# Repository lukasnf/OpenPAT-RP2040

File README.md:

# OpenPAT-RP2040

> **⚠️ SAFETY DISCLAIMER:** This project is for educational and preliminary diagnostic purposes only. While it tests electrical safety parameters, it is **not** a certified Portable Appliance Tester (PAT). It does not replace legally required safety tests conducted with calibrated and certified equipment. Always assume appliances are dangerous until proven otherwise.

**OpenPAT-RP2040** is a low-voltage Portable Appliance Tester based on the RP2040 microcontroller. It is designed to safely measure Protective Earth (PE) continuity at standard test currents (200mA) and verify Phase-to-Neutral (L-N) resistance on **unpowered** appliances. 

Operating completely without high measurement voltages, this design allows for safe preliminary testing of appliances. 

> **Note:** This project is currently under active development. The schematics and PCB layout have been designed using KiCad and manufactured via JLCPCB.

---

## 🛠 Hardware Architecture

The measurement circuitry is designed around the RP2040 and relies on a dedicated analog frontend for precise, low-voltage readings. Based on the schematic, the core components and sub-circuits include:

* **Microcontroller:** RP2040
* **Analog-to-Digital Converter (ADC):** ADS1115 connected via I2C (`I2C_SCL`, `I2C_SDA`) to read the measurement nodes (`PE_TEST`, `PE_TEST_RE`, `L_T`, `N_T`).
* **PE Test Current Source:** A constant current source generating approximately 200mA. This is achieved using an LM317 linear regulator (U1) combined with a 6.2Ω / 1W resistor (R1).
* **PE Continuity Measurement:** Employs a **4-wire (Kelvin) measurement method** to accurately determine resistance by eliminating the voltage drop across the test leads. This is implemented using separate connections for force (`PE_FORCE_IN`, `PE_OUT1`) and sense (`PE_SENSE_1`, which connects to the protected `PE_TEST_RE` node).
* **L-N Resistance Measurement:** Controlled via RP2040 GPIOs. An NMOS transistor (Q1, controlled by GP26) and a switched pull-up (via GP27 and a 1kΩ resistor) are used to configure the circuit to measure the resistance between the Phase and Neutral test points via the L/N_TEST1 connector.
* **Input Protection:** All sensitive analog measurement lines are protected against transients. The circuit uses 10kΩ series resistors (R2, R3, R4, R5) and BAT54S dual Schottky diodes (D1, D2, D3, D4) to safely clamp the ADC inputs to the 3.3V rail and Ground.

## Components

| Component | Value / Type |
| :--- | :--- | 
| Microcontroller | RP2040 Zero 
| ADC | ADS1115 
| N-Channel MOSFET | IRLML 2502 (20V, 4.2A, SOT-23) 
| Schottky Diode | BAT54S-7-F (30V, 0.2A, SOT23) 
| Capacitor | 100 nF (50V, X7R, RM 2.5) 
| Terminal Block | MKDS 1.5/2-5.08 (2-pin, RM 5.08) 
| Shunt Resistor | 6.2 Ω (1 Watt) 
| Standard Resistors | 10 kΩ, 1 kΩ 

## 📂 Repository Contents

...

## 📄 License

This repository contains both hardware design files and software source code, which are licensed differently:

* **Hardware:** All hardware design files (schematics, PCB layouts) are released under the [CERN Open Hardware Licence Version 2 - Strongly Reciprocal (CERN-OHL-S v2)](LICENSE).
* **Software:** All source code is released under the [MIT License](LICENSE-MIT).

This README was drafted with AI assistance. All technical information has been manually verified by the author.

Lukas F.

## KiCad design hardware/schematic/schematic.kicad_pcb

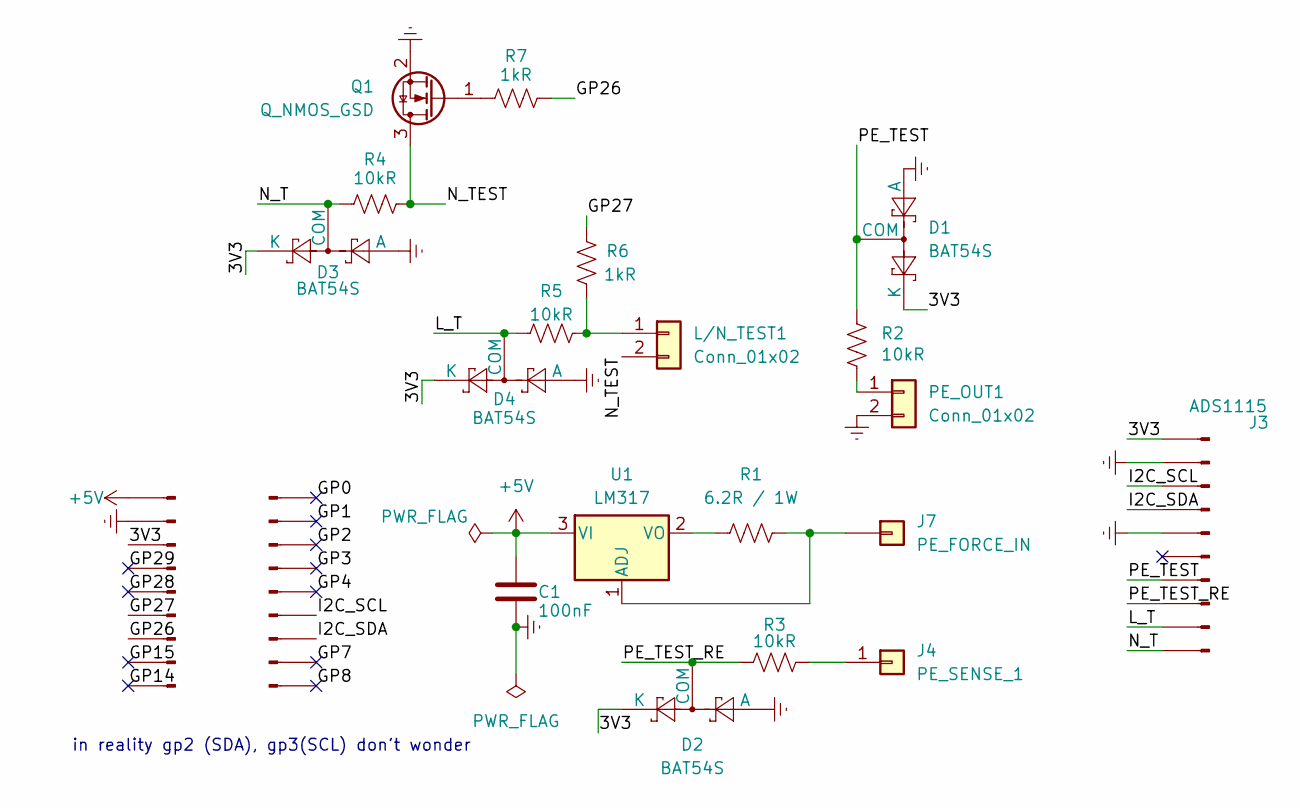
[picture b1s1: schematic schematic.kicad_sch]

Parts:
C1: 100nF; C_Disc_D5.0mm_W2.5mm_P2.50mm
D1, D2, D3, D4: BAT54S; SOT-23; LCSC C83574
J1, J2: Conn_01x09_Pin; PinHeader_1x09_P2.54mm_Vertical
J3: ADS1115; PinHeader_1x10_P2.54mm_Vertical
J4: PE_SENSE_1; PinHeader_1x01_P2.54mm_Vertical
J7: PE_FORCE_IN; PinHeader_1x01_P2.54mm_Vertical
L/N_TEST1: Conn_01x02; TerminalBlock_Phoenix_MKDS-1,5-2-5.08_1x02_P5.08mm_Horizont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
PE_OUT1: Conn_01x02; TerminalBlock_Phoenix_MKDS-1,5-2-5.08_1x02_P5.08mm_Horizont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
Q1: Q_NMOS_GSD; SOT-23; LCSC C20917
R1: 6.2R / 1W; R_Axial_DIN0411_L9.9mm_D3.6mm_P12.70mm_Horizontal
R2, R3, R4, R5: 10kR; R_Axial_DIN0207_L6.3mm_D2.5mm_P10.16mm_Horizontal
R6, R7: 1kR; R_Axial_DIN0207_L6.3mm_D2.5mm_P10.16mm_Horizontal
U1: LM317; TO-220-3_Vertical

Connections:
+5V: C1.1, J2.9, U1.3 (VI)
/3V3: D1.2 (K), D2.2 (K), D3.2 (K), D4.2 (K), J2.7, J3.10
/GP0: J1.1
/GP1: J1.2
/GP2: J1.3
/GP3: J1.4
/GP4: J1.5
/GP7: J1.8
/GP8: J1.9
/GP14: J2.1
/GP15: J2.2
/GP26: J2.3, R7.2
/GP27: J2.4, R6.1
/GP28: J2.5
/GP29: J2.6
/I2C_SCL: J1.6, J3.8
/I2C_SDA: J1.7, J3.7
/L_T: D4.3 (COM), J3.2, R5.1
/N_T: D3.3 (COM), J3.1, R4.1
/N_TEST: L/N_TEST1.2, Q1.3 (D), R4.2
/PE_TEST: D1.3 (COM), J3.4, R2.1
/PE_TEST_RE: D2.3 (COM), J3.3, R3.2
GNDREF: C1.2, D1.1 (A), D2.1 (A), D3.1 (A), D4.1 (A), J2.8, J3.6, J3.9, PE_OUT1.2, Q1.2 (S)
unnamed: J4.1 (Pin_1_1), R3.1
unnamed: J7.1 (Pin_1_1), R1.2, U1.1 (ADJ)
unnamed: L/N_TEST1.1, R5.2, R6.2
unnamed: PE_OUT1.1, R2.2
unnamed: Q1.1 (G), R7.1
unnamed: R1.1, U1.2 (VO)

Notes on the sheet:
in reality gp2 (SDA), gp3(SCL) don't wonder

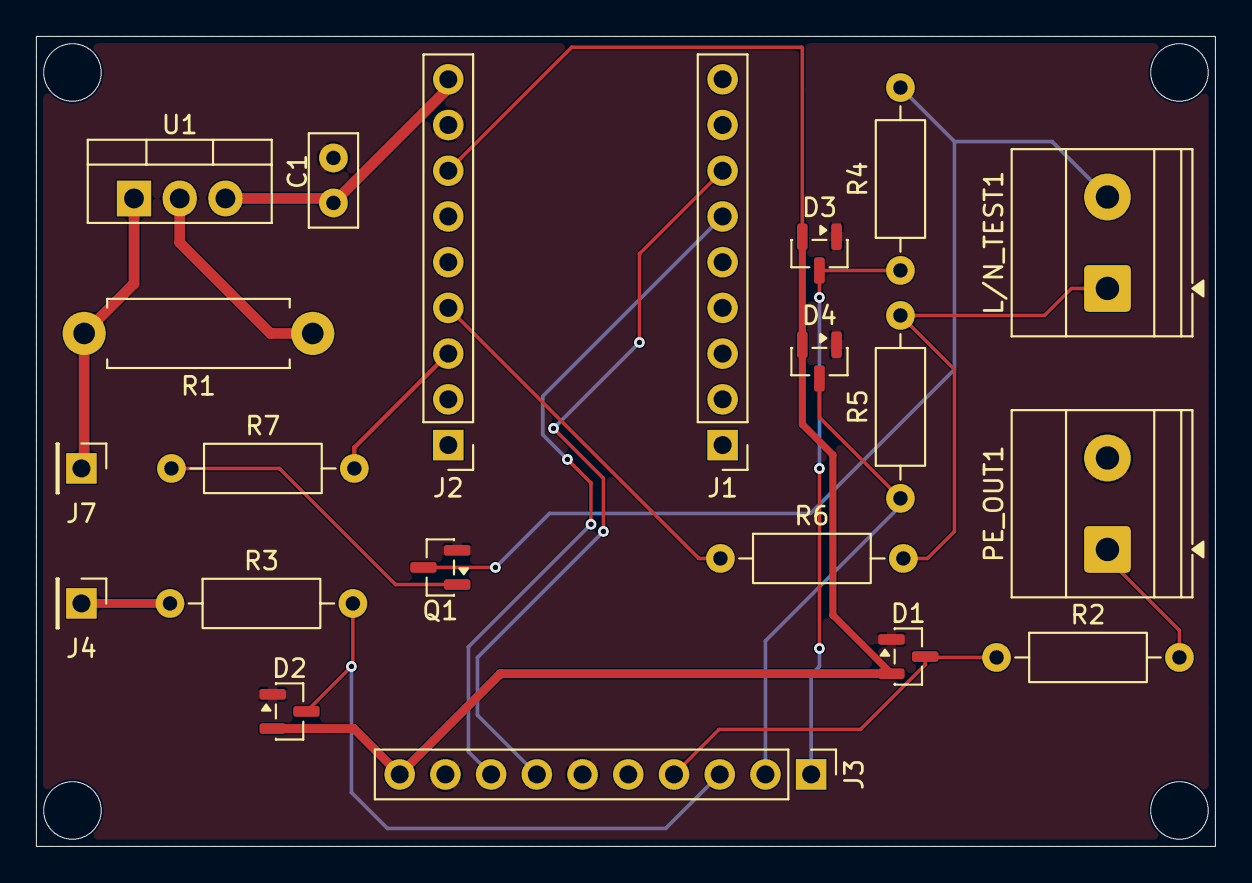
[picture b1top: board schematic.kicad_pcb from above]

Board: 2 copper layers, 65.5 x 45.0 mm, 21 parts (0 on the bottom side), 18 nets.

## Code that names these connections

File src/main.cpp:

#include <Arduino.h>
#include <Wire.h>
#include <Adafruit_ADS1X15.h>

Adafruit_ADS1115 ads; 

// pin definitions
const int MOSFET_GATE = 26; // GPIO 26 for MOSFET gate
const int L_DRIVE = 27; // GPIO 27 for L drive

// ADS pins definitions
const int ADS_PE_HIGH = 0; // PE_TEST_RE
const int ADS_PE_LOW  = 1; // PE_TEST
const int ADS_L_T     = 2; // L_T
const int ADS_N_T     = 3; // N_T

// constants
const float PE_CURRENT_A = 0.195; // current in Amperes for PE TEST
const float R6 = 990.0; // R6 resistance in Ohms
const float RP2040_VCC = 3.224; // output voltage of the RP2040 (3.3V)

void measurePE();
void measureLN();
void setup() {
  Serial.begin(115200);
  
  while (!Serial) {
    delay(10);
  }
  
  delay(2000); 
  Serial.println("\n--- BOOTING OpenPAT-RP2040 ---");

  pinMode(MOSFET_GATE, OUTPUT);
  pinMode(L_DRIVE, OUTPUT);
  digitalWrite(MOSFET_GATE, LOW);
  digitalWrite(L_DRIVE, LOW);

  Wire1.setSDA(2); 
  Wire1.setSCL(3); 
  Wire1.begin();
  
  Serial.println("I2C1 booted");

  if (!ads.begin(0x48, &Wire1)) {
    while (1) {
      Serial.println("Error: ADS1115 not found!");
      delay(1000);
    }
  }

  ads.setGain(GAIN_ONE);
  Serial.println("System ready. Press 'p' for PE-Test, 'l' for L/N-Test");
}

void loop() {
  if (Serial.available() > 0) {
    char input = Serial.read();
    
    if (input == 'P' || input == 'p') {
      measurePE();
    } 
    else if (input == 'L' || input == 'l') {
      measureLN();
    }
    else if (input == 'Q' || input == 'q') {
      digitalWrite(L_DRIVE, LOW);
      digitalWrite(MOSFET_GATE, LOW);
      Serial.println("\n Standby.");
    }
  }
}

void measurePE() {
  Serial.println("\n Starting PE-Test...");

   // differential measurement between ADS_PE_TEST and ADS_PE_TEST_RE
  int16_t adc0_1 = ads.readADC_Differential_0_1();
  
  // calculate the voltage (1 Bit = .125 mV)
  float voltage_PE = (adc0_1 * 0.125) / 1000.0;

  // calculating the resistance of PE
  float resistance_PE = voltage_PE / PE_CURRENT_A;

  // output the results
  Serial.print("Voltaged Drop: "); Serial.print(voltage_PE, 4); Serial.println(" V");
  Serial.print("PE Resistance:   "); Serial.print(resistance_PE, 3); Serial.println(" Ohm");
}


void measureLN() {
  Serial.println("\n Starting L/N-Test...");

  // turn on Mosfet
  digitalWrite(MOSFET_GATE, HIGH);

  // apply voltage to L (via R6)
  digitalWrite(L_DRIVE, HIGH);
  delay(10);

  // measure voltage across L_T and N_T
  int16_t adcL = ads.readADC_SingleEnded(ADS_L_T);
  int16_t adcN = ads.readADC_SingleEnded(ADS_N_T);

  // convert raw ADC values to Volts
  float v_L = (adcL * 0.125) / 1000.0;
  float v_N = (adcN * 0.125) / 1000.0;

  // calculate voltage drop across the DUT
  float voltage_DUT = v_L - v_N;

  // calculate the current through the DUT 
  float current_DUT = (RP2040_VCC - v_L) / R6;

  // calculate the resistance of the DUT
  float resistance_LN = -1; // -1 as default value
  if (current_DUT > 0.0001) { // Prevent division by zero if no load is connected
    resistance_LN = voltage_DUT / current_DUT;
  }

  // Turn everything off 
  digitalWrite(L_DRIVE, LOW);
  digitalWrite(MOSFET_GATE, LOW);

  // output the results
  Serial.print("Voltage at L_T: "); Serial.print(v_L, 3); Serial.println(" V");
  Serial.print("Voltage at N_T: "); Serial.print(v_N, 3); Serial.println(" V");
  
  if (resistance_LN >= 0) {
    Serial.print("L/N Resistance: "); Serial.print(resistance_LN, 1); Serial.println(" Ohm");
  } else {
    Serial.println("L/N Resistance: No continuity");
  }
}
